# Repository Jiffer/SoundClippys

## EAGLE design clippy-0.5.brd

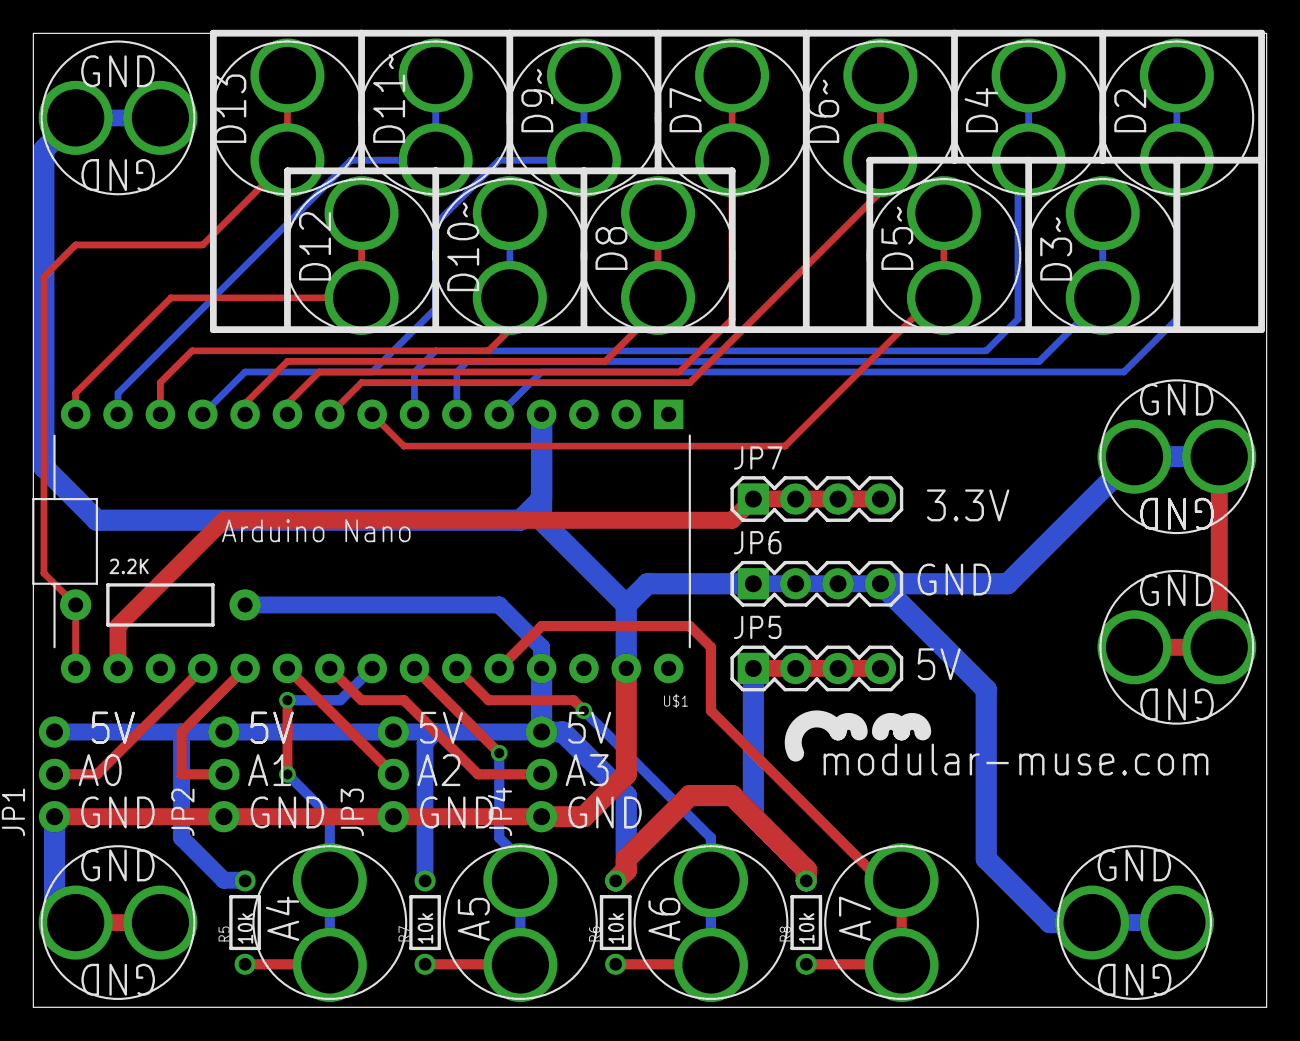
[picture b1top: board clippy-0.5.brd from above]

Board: 2 copper layers, 74.0 x 58.4 mm, 34 parts (0 on the bottom side), 23 nets.

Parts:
2.2K: AXIAL-0.4
JP1, JP2, JP3, JP4: 1X03_NO_SILK
JP5, JP6, JP7: 1X04
R5, R6, R7, R8: 10k; 1/6W-RES
U$1: NANO; MYCON2_HEAD15-NOSS
U$2, U$3, U$4, U$5, U$6, U$7, U$8, U$9, U$10, U$11, U$12, U$13, U$14, U$15, U$16, U$17, U$18, U$19, U$20, U$21, U$22: CLIPPY

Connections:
3.3V: JP7.1, JP7.2, JP7.3, JP7.4, U$1.3V3
5V: 2.2K.P$2, JP1.3, JP2.3, JP3.3, JP4.3, JP5.1, JP5.2, JP5.3, JP5.4, R5.2, R6.2, R7.2, R8.2, U$1.5V
A0: JP1.2, U$1.A0
A1: JP2.2, U$1.A1
A2: JP3.2, U$1.A2
A3: JP4.2, U$1.A3
A4: R5.1, U$1.A4, U$7.1, U$7.2
A5: R7.1, U$1.A5, U$17.1, U$17.2
A6: R6.1, U$1.A6, U$18.1, U$18.2
A7: R8.1, U$1.A7, U$19.1, U$19.2
D2: U$1.D2, U$2.1, U$2.2
D3: U$1.D3, U$3.1, U$3.2
D4: U$1.D4, U$4.1, U$4.2
D5: U$1.D5, U$5.1, U$5.2
D6: U$1.D6, U$6.1, U$6.2
D7: U$1.D7, U$10.1, U$10.2
D8: U$1.D8, U$11.1, U$11.2
D9: U$1.D9, U$12.1, U$12.2
D10: U$1.D10, U$13.1, U$13.2
D11: U$1.D11, U$14.1, U$14.2
D12: U$1.D12, U$15.1, U$15.2
D13: 2.2K.P$1, U$1.D13, U$16.1, U$16.2
GND: JP1.1, JP2.1, JP3.1, JP4.1, JP6.1, JP6.2, JP6.3, JP6.4, U$1.GND, U$1.GND2, U$8.1, U$8.2, U$9.1, U$9.2, U$20.1, U$20.2, U$21.1, U$21.2, U$22.1, U$22.2

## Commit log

2016-06-07 Sound Clippys Eagle files
    Initial commit

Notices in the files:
parts and their libraries:
SparkFun-Connectors: Licensing: Creative Commons ShareAlike 4.0 International - https://creativecommons.org/licenses/by-sa/4.0
